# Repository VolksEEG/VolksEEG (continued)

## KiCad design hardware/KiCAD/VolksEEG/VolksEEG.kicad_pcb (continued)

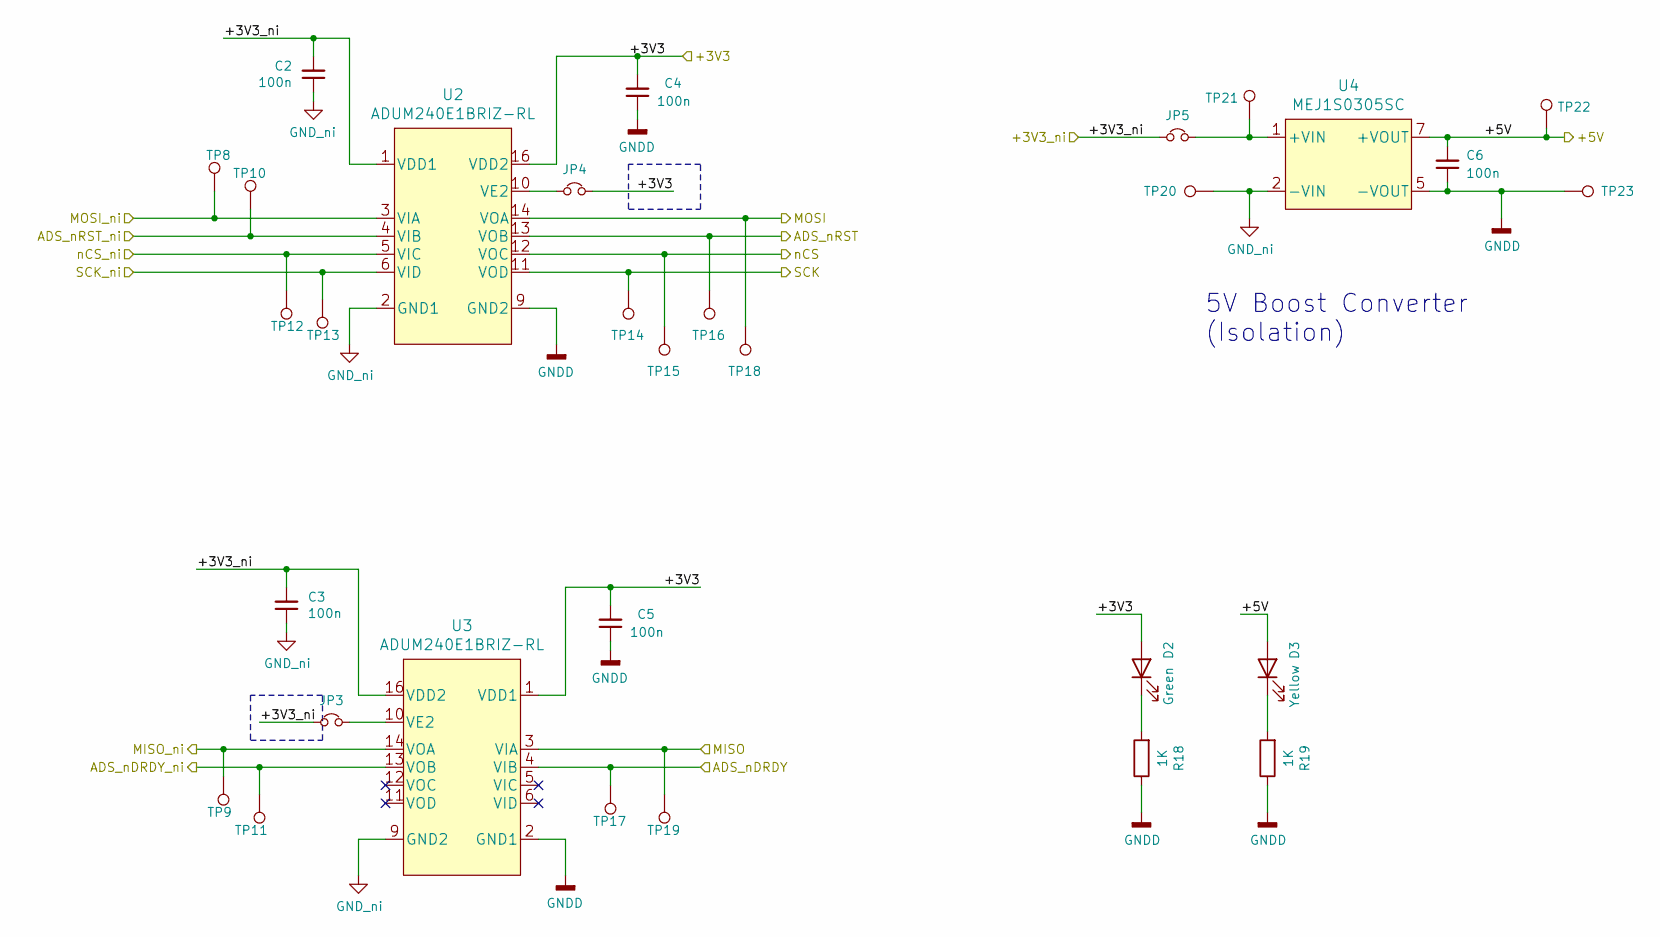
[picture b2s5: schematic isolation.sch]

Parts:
C2, C3, C4, C5, C6: 100n; C_0603_1608Metric_Pad1.08x0.95mm_HandSolder; Part Number CL21B104KACNNNC
D2: Green; LED_0603_1608Metric_Pad1.05x0.95mm_HandSolder; Part Number VFHL1116P-4BX3C-TR
D3: Yellow; LED_0603_1608Metric_Pad1.05x0.95mm_HandSolder; Part Number VFHY1104P-4C42D-TR
JP3, JP4, JP5: Jumper_NC_Small; SolderJumper-2_P1.3mm_Bridged_Pad1.0x1.5mm; Part Number N/A
R18, R19: 1K; R_0603_1608Metric_Pad0.98x0.95mm_HandSolder; Part Number RMCF0603FG1K00
TP8, TP9, TP10, TP11, TP12, TP13, TP14, TP15, TP16, TP17, TP18, TP19, TP20, TP21, TP22, TP23: TestPoint; TestPoint_Keystone_5010-5014_Multipurpose; Part Number N/A
U2, U3: ADUM240E1BRIZ-RL; SOIC-16W_7.5x12.8mm_P1.27mm; Part Number ADUM240E1BRIZ-RL
U4: MEJ1S0305SC; 7SIP; Part Number MEJ1S0305SC

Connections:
/ADS1299 Power/+3V3: C4.2, C5.2, D2.2 (A), JP4.2, U2.16 (VDD2), U3.1 (VDD1); also elsewhere on the board
/ADS1299 Power/+5V: C6.2, D3.2 (A), TP22.1, U4.7 (+VOUT); also elsewhere on the board
/ADS1299/ADS_nDRDY: TP17.1, U3.4 (VIB); also elsewhere on the board
/ADS1299/ADS_nRST: TP16.1, U2.13 (VOB); also elsewhere on the board
/ADS1299/MISO: TP19.1, U3.3 (VIA); also elsewhere on the board
/ADS1299/MOSI: TP18.1, U2.14 (VOA); also elsewhere on the board
/ADS1299/SCK: TP14.1, U2.11 (VOD); also elsewhere on the board
/ADS1299/nCS: TP15.1, U2.12 (VOC); also elsewhere on the board
/Isolation/+3V3_ni: C2.2, C3.2, JP3.1, JP5.1, U2.1 (VDD1), U3.16 (VDD2); also elsewhere on the board
/Isolation/MISO_ni: TP9.1, U3.14 (VOA); also elsewhere on the board
/Isolation/MOSI_ni: TP8.1, U2.3 (VIA); also elsewhere on the board
/Isolation/SCK_ni: TP13.1, U2.6 (VID); also elsewhere on the board
/nRF52840 Feather Sense Express Board/ADS-nCS_ni: TP12.1, U2.5 (VIC); also elsewhere on the board
/nRF52840 Feather Sense Express Board/ADS-nDRDY_ni: TP11.1, U3.13 (VOB); also elsewhere on the board
/nRF52840 Feather Sense Express Board/ADS-nRST_ni: TP10.1, U2.4 (VIB); also elsewhere on the board
GND: C2.1, C3.1, TP20.1, U2.2 (GND1), U2.8 (GND1), U3.9 (GND2), U3.15 (GND2), U4.2 (-VIN); also elsewhere on the board
GNDD: C4.1, C5.1, C6.1, R18.1, R19.1, TP23.1, U2.9 (GND2), U2.15 (GND2), U3.2 (GND1), U3.8 (GND1), U4.5 (-VOUT); also elsewhere on the board
unnamed: D2.1 (K), R18.2
unnamed: D3.1 (K), R19.2
unnamed: JP3.2, U3.10 (VE2)
unnamed: JP4.1, U2.10 (VE2)
unnamed: JP5.2, TP21.1, U4.1 (+VIN)

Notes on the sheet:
5V Boost Converter (Isolation)

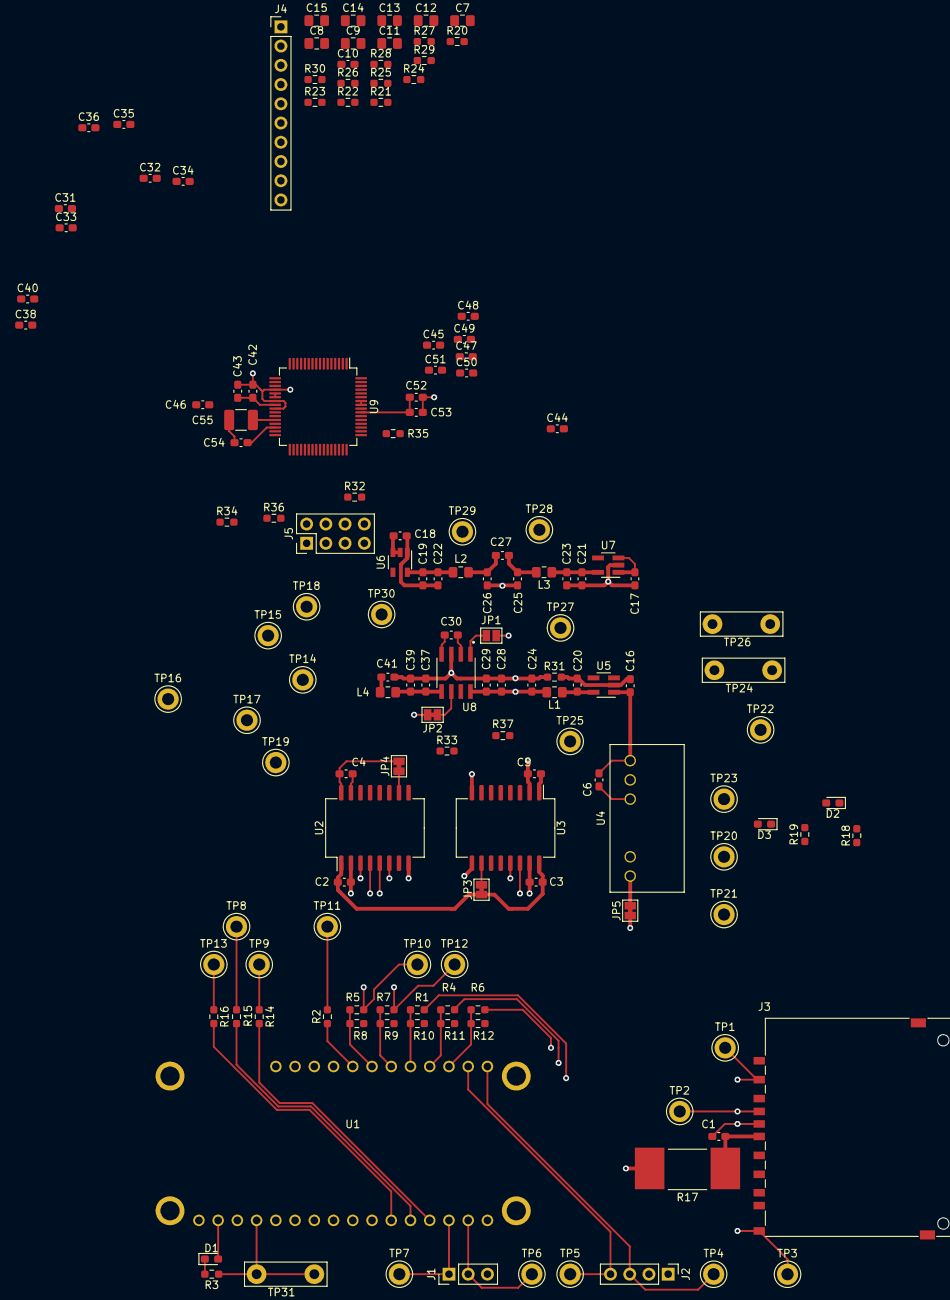
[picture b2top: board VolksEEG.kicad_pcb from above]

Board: 4 copper layers, 148 parts (0 on the bottom side), 85 nets.

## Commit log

2021-04-23 Added power supply photo
2021-04-23 Added photo
2021-04-23 Renamed photo (removed spaces) to make github happy
2021-04-23 Deleted unused image, added new image
2021-05-28 Create test_generator_2.edf
    Added test edf file
2021-05-29 start of setting up to send HID
2021-05-29 cleaned up
2021-08-04 PCB: add Altium project
2021-08-20 Update README.md
    First draft of readme file
2021-08-20 Create EE Architecture Block DIagram 2.png
    Added updated EE block diagram
2021-08-20 Update README.md
    Added image to readme
2021-08-20 Update README.md
    Adding image, try #2
2021-08-20 Update EE Architecture Block DIagram 2.png
    Tweaked diagram
2021-08-21 Added SD card to block diagram
2021-08-21 Update README.md
    Updated to reference updated block diagram
2021-08-21 Revert "Update README.md"
    This reverts commit 685a839cfd17837975c035cd202eaa9641504920.
2021-08-21 Update README.md
    Added description of SD card usage
2021-09-05 Added screen capture of 32-channel UI display POC
2021-09-05 Added POC waveform video,
2021-09-06 Update README.md
    Cleaned up a little, added link to Project Overview
2021-09-06 Update README.md
    Fixing goofs from last commit
2021-09-06 Update README.md
    Fixing another goof. I must need coffee.
2021-09-11 Update README.md
    Editing
2021-09-27 Added updated block diagram
2021-09-27 Update README.md
    Updated block diagram.
2021-10-01 Update README.md
    Added link to volkseeg.org
2021-10-02 ADS, nRF, electrodes added to lib and sch
2021-10-02 pcb directory restructurated
2021-10-02 Input and inverting power supply added
2021-10-02 OuputJob file added and BOM generated
2021-10-05 Progress in transfer Altium to KiCAD
2021-10-05 Added draft specifications
2021-10-07 power supply finished
2021-10-10 pcb layout update
2021-10-21 Initial commit of firmware project.
2021-10-21 Initial commit of firmware test.
2021-10-21 Small change in readme file to see if push is working
2021-10-21 Another small tweak in readme to test git
2021-10-22 Commit of Firmware to it's own Branch.
2021-10-22 Removed Fimware from main, this is now in it's own branch to allow github actions to run.
2021-10-22 Started adding schematic sheet for isolation.
2021-10-22 re-organised the root schematic, plumbed in the power and signal lines. renamed the nrf52840 sheet to highlight the fact it is the Feather Sense Express board.
2021-10-23 Some re-naming and added some pull ups to the nrf schematic.
2021-10-23 Added Digi-key's kicad component libraries, some work done on power, think this will change but capturing it here for posterity.
2021-10-23 Rejigged the power around so that the 3v3 supply is only generated once.
2021-10-25 Update README.md
    Fixed typo
2021-10-25 Update README.md
    Added section on why we don't need detailed requirements and specs to start
2021-10-25 Updating analogue inputs to the referential montage and connected a few ADS1299 pins.
2021-10-26 Added list of known remaining tasks on the schematic.
2021-10-26 Added more tasks following re-watch of 1st half of previous design review.
2021-10-26 Updated names of heirarchical pins, finished referential montage configuration, added filter cap to ADS_nRST line, started putting ADS1299 gpios to a header.
2021-10-26 Added custom power symbols for non isolated power. Seperated Analogue and digital supplies. finished putting the ADS1299 GPIOs to a header.
2021-10-27 Tweaks based on feedback, Changed digital isolators to ADUM240E devices due to component availability.
2021-10-27 Changed -2.5V Regulator due to part availability.
2021-10-27 Added debugging bits to the NRF schematic sheet.
2021-10-28 Added debugging bits to more schematic sheets.
2021-10-28 tweaks to the ADS1299 schematic.
2021-10-29 finished off tasks list.
2021-10-30 Added start of Protocol Frame Parser Added PinControl (HAL) class and added test modules for each of these new classes. Added MyDelay library to control heartbeat LED timing.
2021-10-31 Refactor following suggestions from Harry and Steve. Added CppCheck Github Ation.
2021-10-31 Added PinControl functions for other GPIO pins. Added build Github Action.
2021-10-31 Replaced seperate Github Actions with Single Action with dependent steps.
2021-10-31 Added missing Steps:
2021-10-31 Indented run:'s
2021-10-31 Removed Setup job as this was not shared with other Jobs as expected. Now reinstalling environment for each Job.
2021-11-02 Removed gnd-ni.lib reference from project libraries.
    This library is not included in the repo and the gnd-ni symbol is already in the VolksEEG.lib file.
2021-11-02 Added KiCAD specific .gitignore and removed unnecessary backup files.
2021-11-02 Removed deprecated Altium files.
2021-11-02 Changed ADuM420 sch symbol to more KiCAD-like look.
2021-11-02 Changed MEJ1S sch symbol to be more KiCAD-like.
2021-11-10 Adding "debug_tool = jlink" to build configs
2021-11-14 Cleaned up nrf page and converted +3V3_ni to non-global symbols.
2021-11-14 Updated schem symbol for ADP7182.
    Converted symbol to be more KiCAD-like.
    This includes stacking the pins, removing the NC pins, and making the background yellow.
2021-11-14 Fixed an bug with the global power nets being used.
    The use of global power nets caused the +3V3A, +3V3, and -3V3A nets to be shorted together.
2021-11-14 Updated schem symbols on Power sheet.
    Updated symbols to remove NC pins.
    Updated pcb footprints to use default SOT-23-5 rather than custom footprint, and deleted custom footprint.
2021-11-14 Removed custom global power symbols to prevent the bug from happening again.
2021-11-14 Annotated schematic and cleared ERC errors.
2021-11-14 Cleaned up ADS1299 page.
2021-11-15 General schematic cleanup, and assigning some footprints.
    Cleaning up the meta-data within KiCAD, and assigning some basic footprints.
    Also, cleaning out some footprint references that didn't point anywhere.
2021-11-15 Change ADS1299 over to using the KiCAD library footprint.
    Also deleted the custom drawn QFP footprint.
2021-11-28 Update README.md
    Added links to PC Software and firmware repositories.
2021-12-11 Updated some footprints and part manufacturers and numbers.
2021-12-12 Photos for Rust Dev Adafruit nRF52840 Feather Express Wiki
2021-12-12 Finished adding footprints, and started laying out the isolation section.
2021-12-15 Layout of the NRF52840 section of the PCB.
2022-01-09 Further PCB Layout.
2022-04-09 Added initial work on Dev board.
2022-04-09 Added revision and 'Not for use as a medical device' to the silkscreen.
2022-04-10 adjusted board dimensions slightly and regenerated Gerbers.
2022-07-05 added components, initial connections
2022-07-08 Fixed some net names on schematic
2022-07-08 Updates
    WIP
2022-07-08 Added Visual Studio Stuff
    I don't know where it came from...
2022-07-09 Ready for schematic review
    Besides changing net names and so forth:
    - Changed Feather 3V pin to output
    - Added ADS1299EEGFE-PDK to VolksEEG symbol library
    - Added Adafruit_SD_Breakout to VolksEEG symbol library
    ERC complains that three switches should be updated from library, can't seem to fix that
2022-07-09 Added video of prototype UI
2022-07-09 Revert "Added video of prototype UI"
    This reverts commit 8652e89c198d57db21fe4f76202bbbf2b087be41.
2022-07-10 As sent to JLBPC
2022-07-13 Cleared out KiCAD backups, and added .gitignore for dev boards.
2022-07-31 Update README.md
    Updated, somewhat restructured
2022-07-31 Update README.md
    Previous update was an accident. This is actually an update!
